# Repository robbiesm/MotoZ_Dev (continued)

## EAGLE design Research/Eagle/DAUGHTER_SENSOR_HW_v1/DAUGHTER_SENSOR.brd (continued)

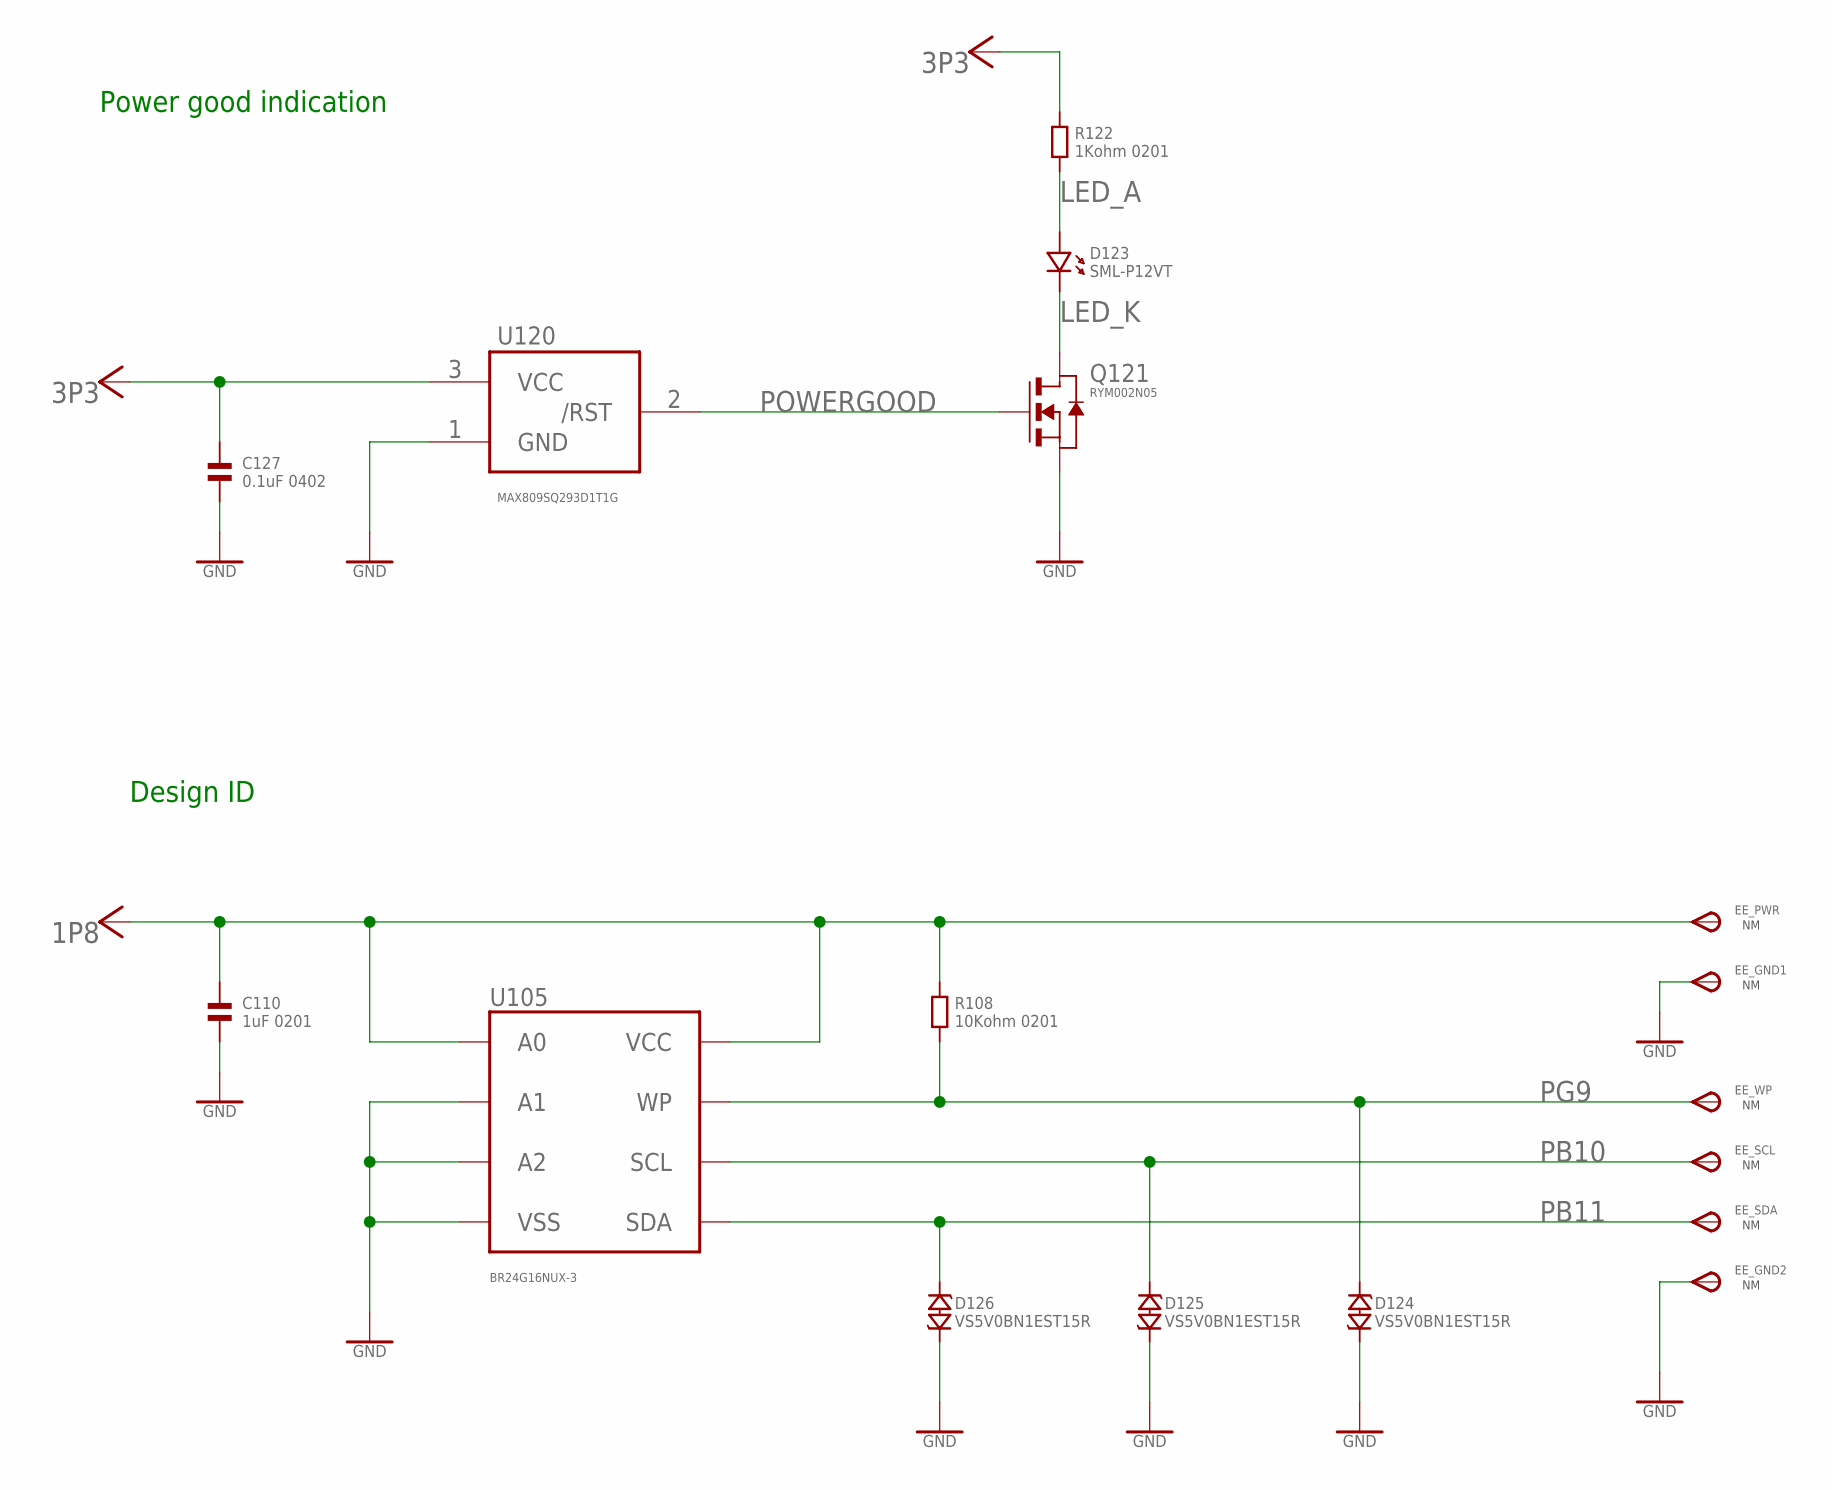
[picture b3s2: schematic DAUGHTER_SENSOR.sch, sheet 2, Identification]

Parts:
C110: 1uF 0201; 0201
C127: 0.1uF 0402; 0402
D123: SML-P12VT; 0503.LED
D124, D125, D126: VS5V0BN1EST15R; CHIP_0201
EE_GND1, EE_GND2: NM; TP11R
EE_PWR: NM; TP11R
EE_SCL: NM; TP11R
EE_SDA: NM; TP11R
EE_WP: NM; TP11R
Q121: RYM002N05; VMT3
R108: 10Kohm 0201; 0201
R122: 1Kohm 0201; 0201
U105: BR24G16NUX-3; DFN-8
U120: MAX809SQ293D1T1G; SC70-3L

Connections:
1P8: C110.1, EE_PWR.TP, R108.1, U105.P$1 (A0), U105.P$8 (VCC); also elsewhere on the board
3P3: C127.1, R122.1, U120.3 (VCC); also elsewhere on the board
GND: C110.2, C127.2, D124.P$2 (2), D125.P$2 (2), D126.P$2 (2), EE_GND1.TP, EE_GND2.TP, Q121.2 (S), U105.P$2 (A1), U105.P$3 (A2), U105.P$4 (VSS), U105.P$9 (VSS), U120.1 (GND); also elsewhere on the board
LED_A: D123.P$1 (1), R122.2
LED_K: D123.P$2 (2), Q121.3 (D)
PB10: D125.P$1 (1), EE_SCL.TP, U105.P$6 (SCL); also elsewhere on the board
PB11: D126.P$1 (1), EE_SDA.TP, U105.P$5 (SDA); also elsewhere on the board
PG9: D124.P$1 (1), EE_WP.TP, R108.2, U105.P$7 (WP); also elsewhere on the board
POWERGOOD: Q121.1 (G), U120.2 (/RST)

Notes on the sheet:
Power good indication
Design ID

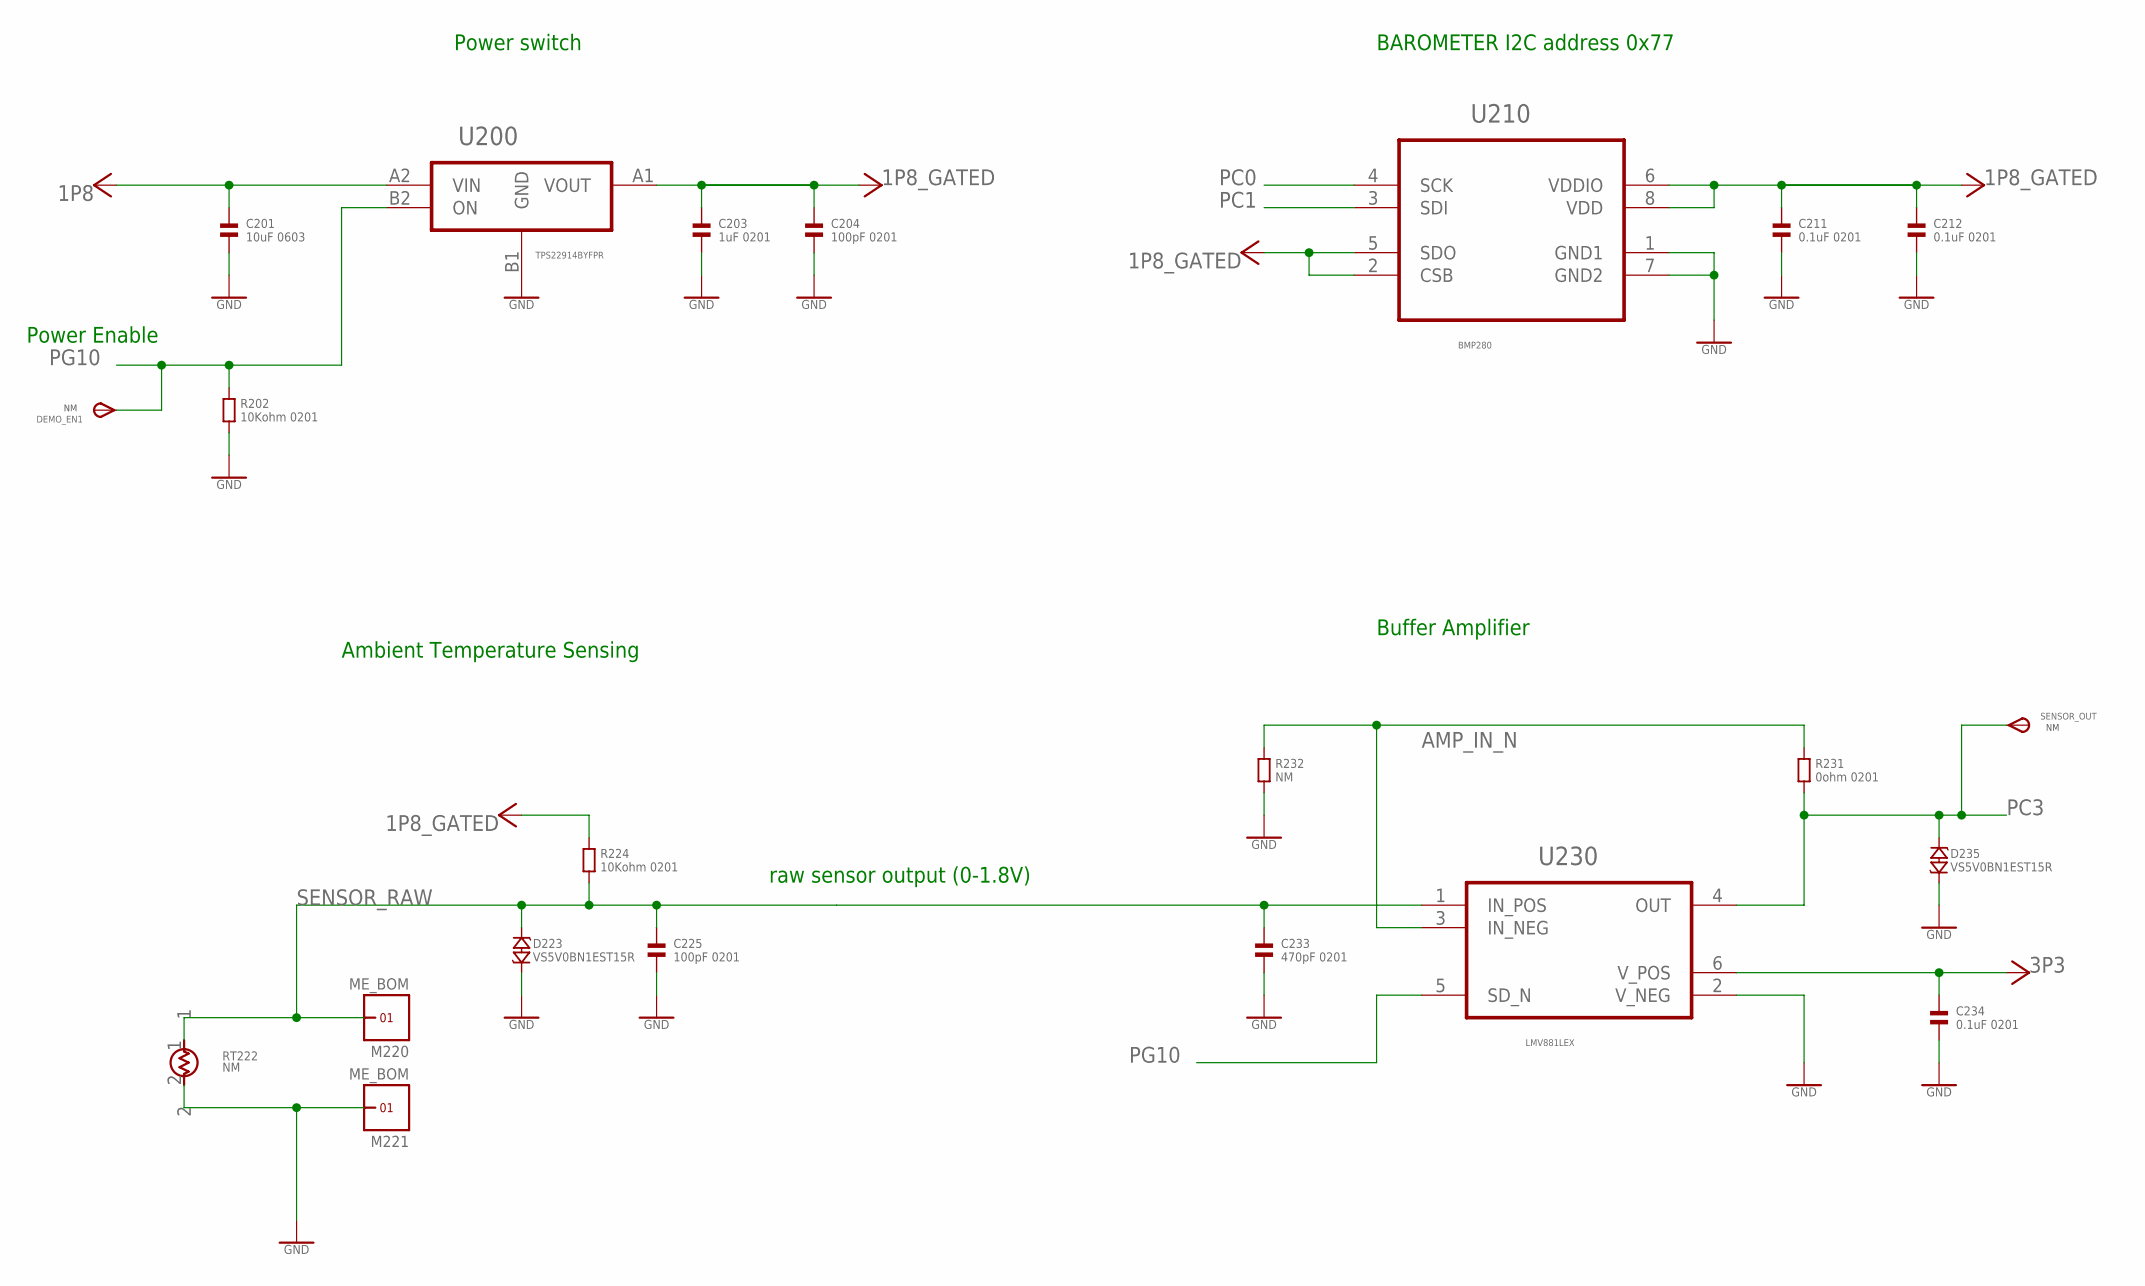
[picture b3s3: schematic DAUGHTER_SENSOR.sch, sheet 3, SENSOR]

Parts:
C201: 10uF 0603; 0603
C203: 1uF 0201; 0201
C204, C225: 100pF 0201; 0201
C211, C212, C234: 0.1uF 0201; 0201
C233: 470pF 0201; 0201
D223, D235: VS5V0BN1EST15R; CHIP_0201
DEMO_EN1: NM; TP11R
M220, M221: ME_BOM; UNIVERSAL_CONTACT
R202, R224: 10Kohm 0201; 0201
R231: 0ohm 0201; 0201
R232: NM; 0201
RT222: NM; 0201
SENSOR_OUT: NM; TP11R
U200: TPS22914BYFPR; BGA0_75SQ_PS0_4_P4
U210: BMP280; LGA2X2_5PS0_65_P8
U230: LMV881LEX; DFN1_5X1PS0_5P6

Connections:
1P8: C201.1, U200.A2 (VIN); also elsewhere on the board
1P8_GATED: C203.1, C204.1, C211.1, C212.1, R224.1, U200.A1 (VOUT), U210.2 (CSB), U210.5 (SDO), U210.6 (VDDIO), U210.8 (VDD)
3P3: C234.1, U230.6 (V_POS); also elsewhere on the board
AMP_IN_N: R231.1, R232.1, U230.3 (IN_NEG)
GND: C201.2, C203.2, C204.2, C211.2, C212.2, C225.2, C233.2, C234.2, D223.P$2 (2), D235.P$2 (2), M221.G1, R202.2, R232.2, RT222.2, U200.B1 (GND), U210.1 (GND1), U210.7 (GND2), U230.2 (V_NEG); also elsewhere on the board
PC0: U210.4 (SCK); also elsewhere on the board
PC1: U210.3 (SDI); also elsewhere on the board
PC3: D235.P$1 (1), R231.2, SENSOR_OUT.TP, U230.4 (OUT); also elsewhere on the board
PG10: DEMO_EN1.TP, R202.1, U200.B2 (ON), U230.5 (SD_N); also elsewhere on the board
SENSOR_RAW: C225.1, C233.1, D223.P$1 (1), M220.G1, R224.2, RT222.1, U230.1 (IN_POS)

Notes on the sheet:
Power Enable
BAROMETER I2C address 0x77
Power switch
Buffer Amplifier
Ambient Temperature Sensing
raw sensor output (0-1.8V)

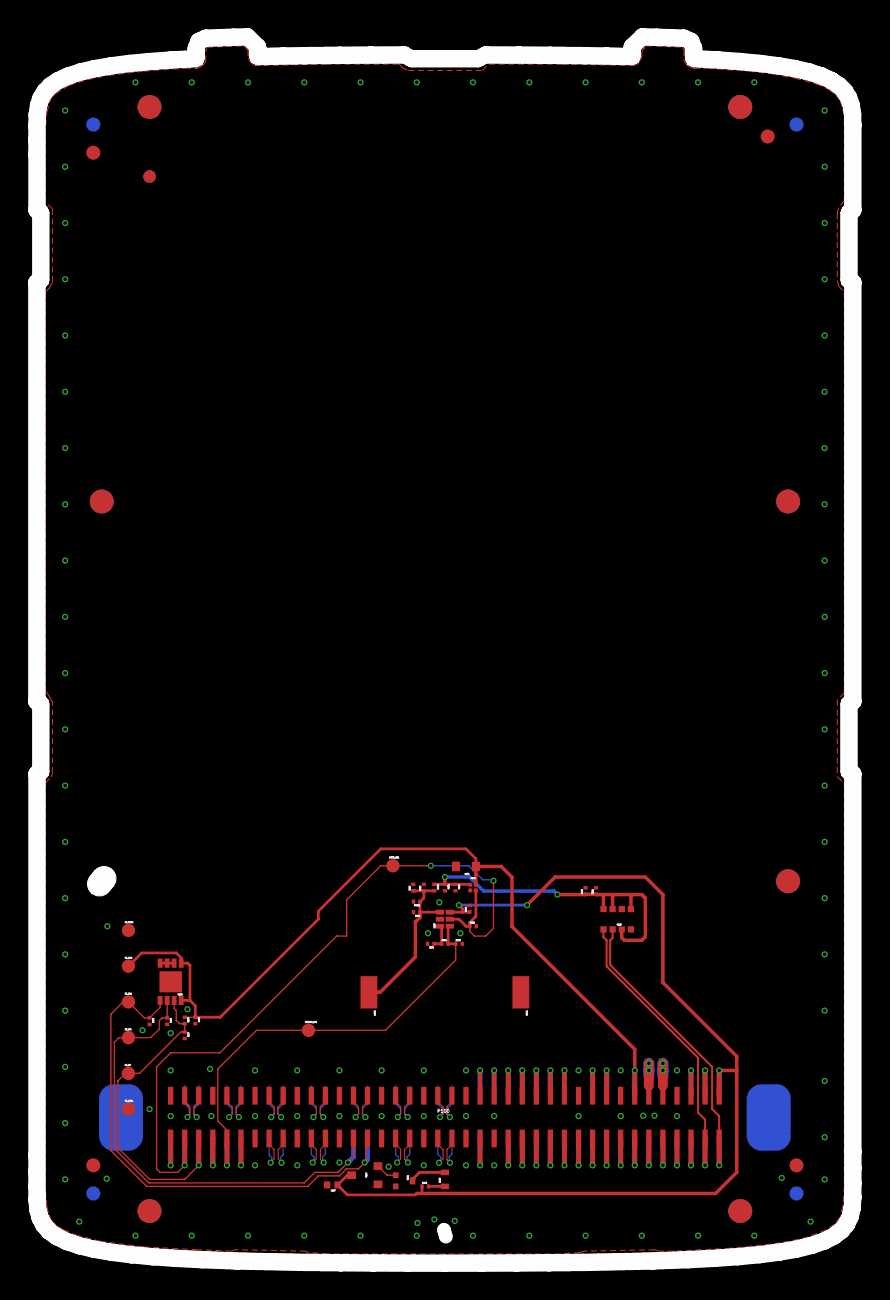
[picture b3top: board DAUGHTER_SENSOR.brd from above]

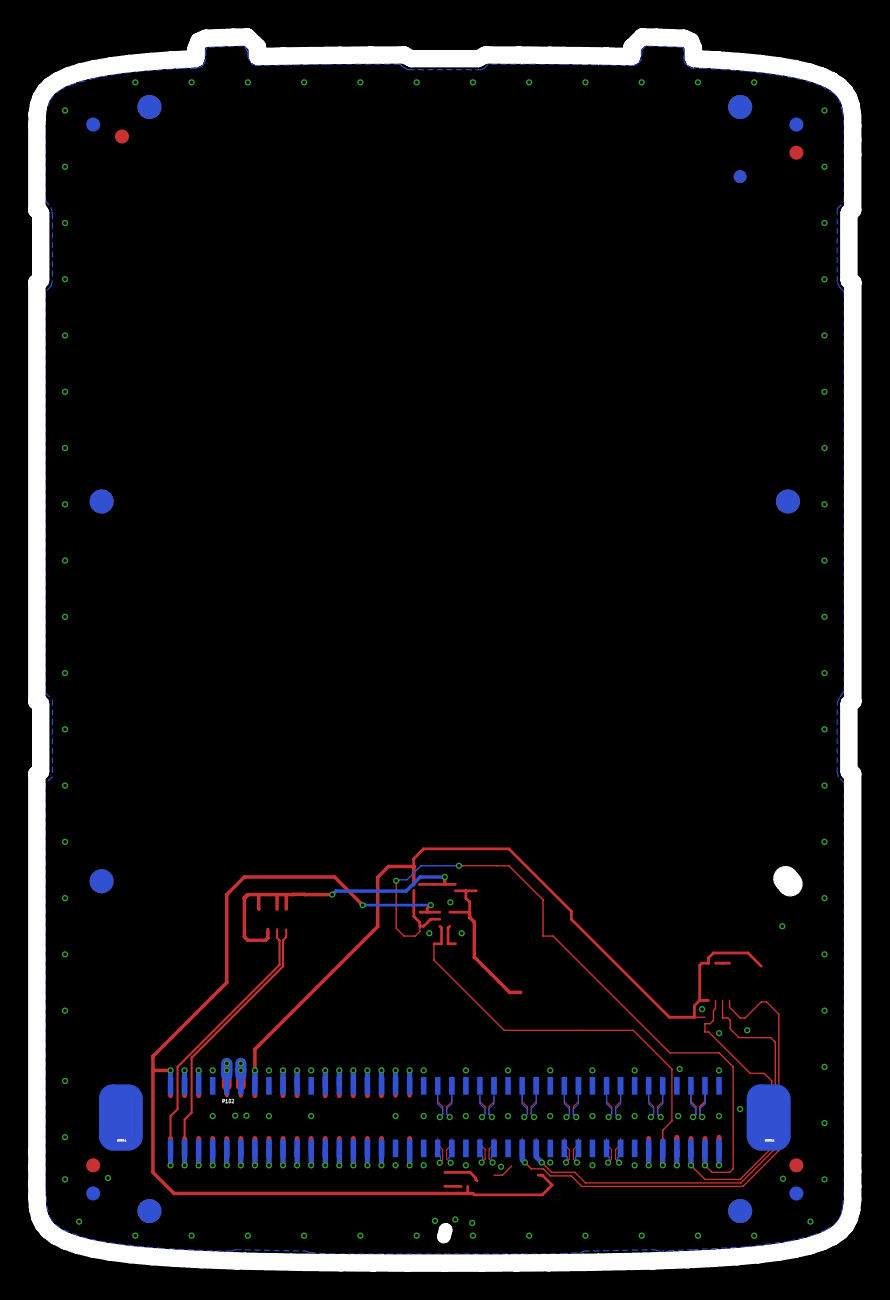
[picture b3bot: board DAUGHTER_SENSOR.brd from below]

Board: 4 copper layers, 58.1 x 87.2 mm, 43 parts (3 on the bottom side), 69 nets.

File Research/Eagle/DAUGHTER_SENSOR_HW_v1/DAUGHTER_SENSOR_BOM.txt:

Partlist exported at 7/24/2016 8:33 PM

Qty Value            Device                   Package                  Parts                                                                 Description                                     MPN                                  SUPPLIER     
3   0.1uF 0201       CAPACITOR.0201           0201                     C211, C212, C234                                                      Ceramic Capacitor, Generic                                                                        
1   0.1uF 0402       CAPACITOR.0402           0402                     C127                                                                  Ceramic Capacitor, Generic                                                                        
1   0ohm 0201        RESISTOR.0201            0201                     R231                                                                  Resistor - Generic                                                                                
2   100pF 0201       CAPACITOR.0201           0201                     C204, C225                                                            Ceramic Capacitor, Generic                                                                        
3   10Kohm 0201      RESISTOR.0201            0201                     R108, R202, R224                                                      Resistor - Generic                                                                                
1   10uF 0603        CAPACITOR.0603           0603                     C201                                                                  Ceramic Capacitor, Generic                                                                        
1   1Kohm 0201       RESISTOR.0201            0201                     R122                                                                  Resistor - Generic                                                                                
2   1uF 0201         CAPACITOR.0201           0201                     C110, C203                                                            Ceramic Capacitor, Generic                                                                        
1   470pF 0201       CAPACITOR.0201           0201                     C233                                                                  Ceramic Capacitor, Generic                                                                        
1   ASP-193073-01    FTMH-140-02-L-DV-ES-P-TR FTMH-140-02-L-DV-ES-P-TR P102                                                                  MICRO SOCKET, 1.0MM, SMD, 2X40WAY, MALE         ASP-193073-01                        SAMTEC       
1   BMP280           BMP280                   LGA2X2_5PS0_65_P8        U210                                                                  BAROMETER BMP280                                BMP280                               BOSCH        
1   BR24G16NUX-3     EEPROMDFN8               DFN-8                    U105                                                                  I2C EE PROM, 8 pin                              BR24G16NUX-3                         ROHM         
1   LMV881LEX        LMV881LEX                DFN1_5X1PS0_5P6          U230                                                                  LOW NOISE OPAMP with Shutdown.                  LMV881LEX                            TI           
1   MAX809SQ293D1T1G MAX809                   SC70-3L                  U120                                                                  3-Pin Microprocessor Reset Circuit              MAX809SQ293D1T1                      ON-SEMI      
2   ME_BOM           SHIELDDETECT             PLUG                     DETECT_1, DETECT_2                                                    Shield, Custom                                  refer to ME BOM                      ref to ME BOM
2   ME_BOM           UNVERSA_CONTACT          UNIVERSAL_CONTACT        M220, M221                                                            Universal contact, Generic                      refer to ME BOM                      ref to ME BOM
1   NM               CLM-140-02-L-D-KGOLD     CLM-140-02-L-D-K_GOLD    P100                                                                  MICRO SOCKET, 1.0MM pitch, SMD, 2X40WAY, Female CLM-140-02-L-D-K                     SAMTEC       
1   NM               RESISTOR.0201            0201                     R232                                                                  Resistor - Generic                                                                                
1   NM               THERMISTOR               0201                     RT222                                                                 Thmistor, NTC 10Khm 3%, 0201                    NCP03XV103XV103E05RL/NTCG0603UH103HT MURARA/TDK   
8   NM               TPSTP11R                 TP11R                    DEMO_EN1, EE_GND1, EE_GND2, EE_PWR, EE_SCL, EE_SDA, EE_WP, SENSOR_OUT TEST Point, 1mm diameter, gold                                                                    
1   RYM002N05        FET-NRYM002N05           VMT3                     Q121                                                                  Generic NMOS FET                                RYM002N05                            ROHM         
1   SML-P12VT        LED.0503                 0503.LED                 D123                                                                  LED GENERIC, single, 2 pin                      SML-P12VT                            ROHM         
1   TPS22914BYFPR    TPS22914BYFPR            BGA0_75SQ_PS0_4_P4       U200                                                                  5V load switch                                  TPS22914BYFPR                        TI           
5   VS5V0BN1EST15R   ESD_VARISTOR.0201        CHIP_0201                D124, D125, D126, D223, D235                                          GENERIC varistor,single, 2 pin                  VS5V0BN1EST15R                       ROHM

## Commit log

2018-05-24 :circus_tent: Added .gitattributes & .gitignore files
2018-05-24 Added and classified files for motorola website
